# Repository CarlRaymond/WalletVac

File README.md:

# WalletVac
A unique donation accepting device

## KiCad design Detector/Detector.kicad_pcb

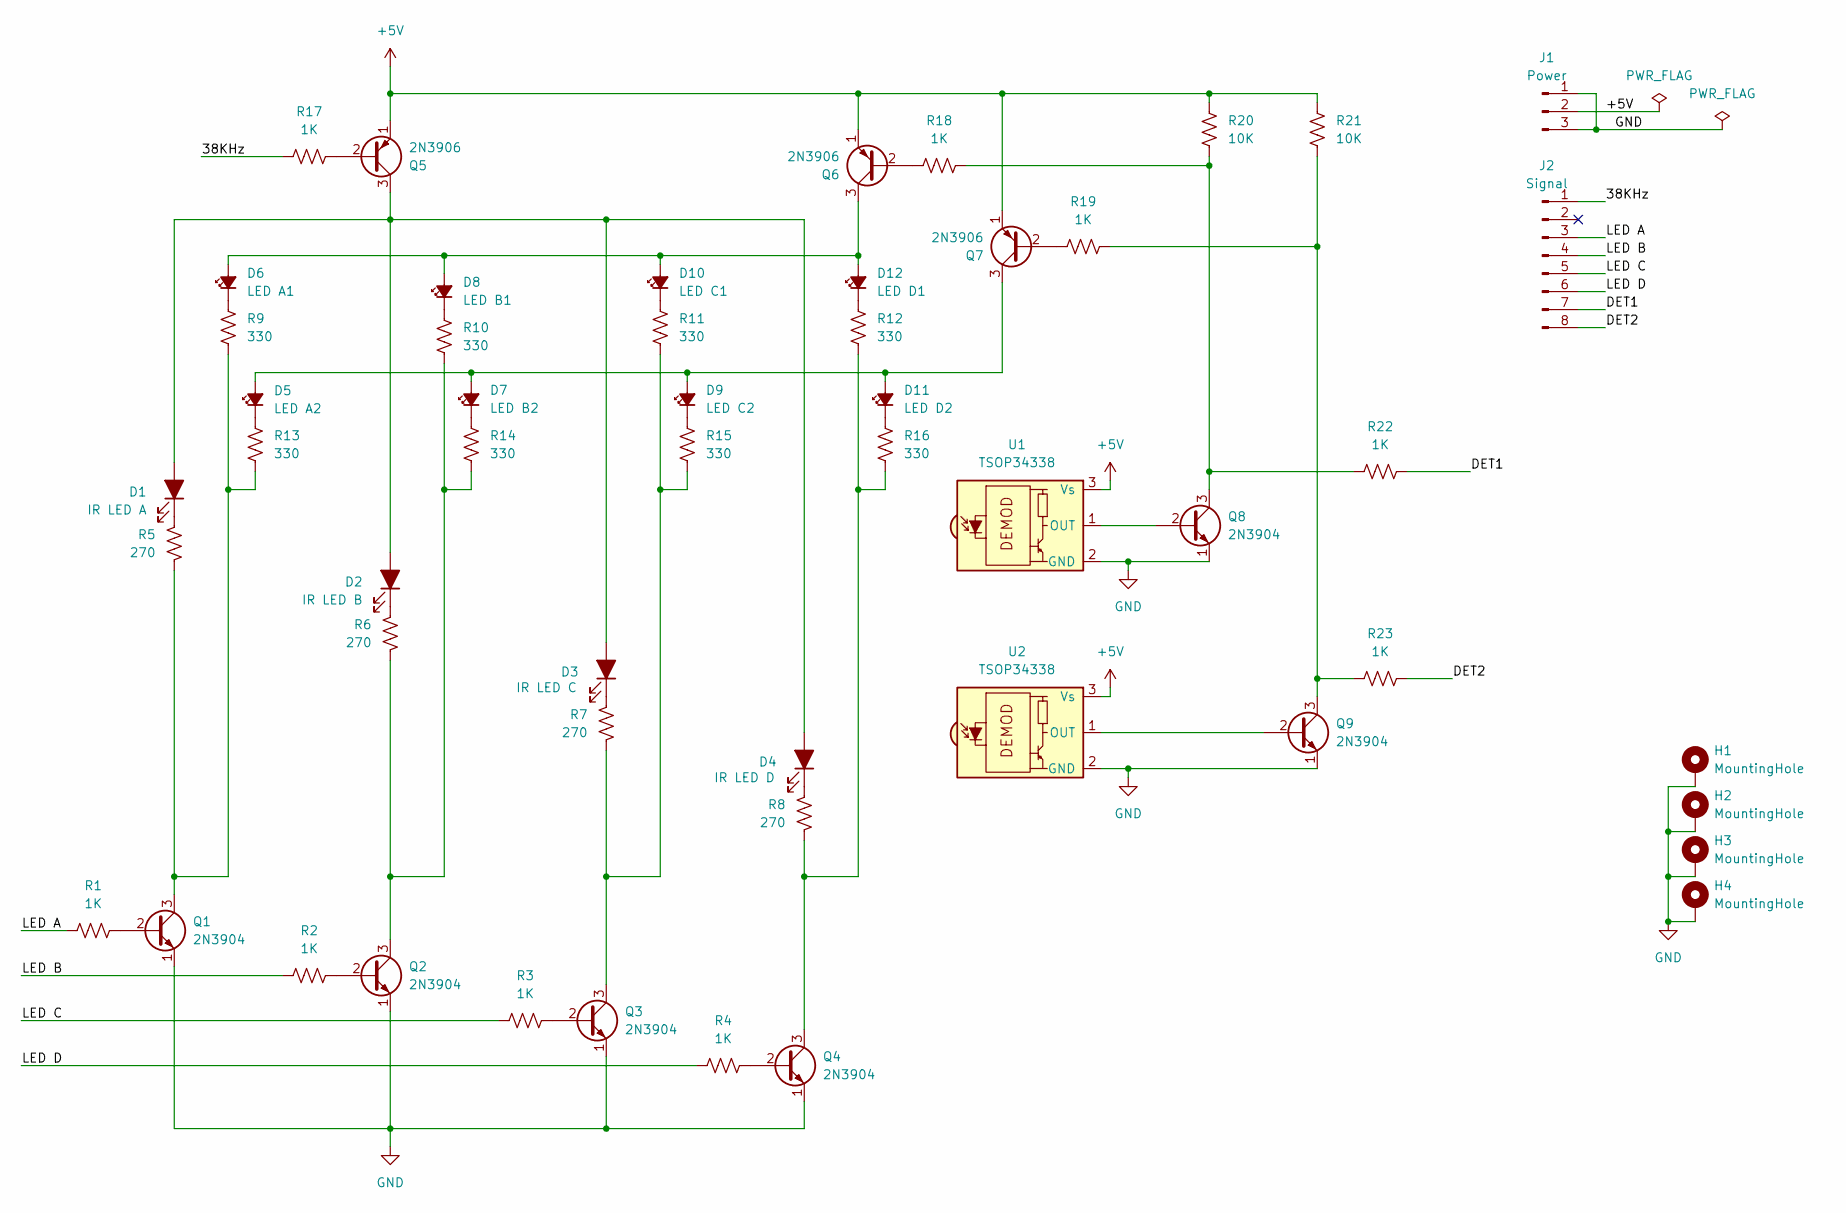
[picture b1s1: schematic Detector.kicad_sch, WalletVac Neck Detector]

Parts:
D1: IR LED A; LED_D5.0mm_Horizontal_O3.81mm_Z3.0mm
D2: IR LED B; LED_D5.0mm_Horizontal_O3.81mm_Z3.0mm
D3: IR LED C; LED_D5.0mm_Horizontal_O3.81mm_Z3.0mm
D4: IR LED D; LED_D5.0mm_Horizontal_O3.81mm_Z3.0mm
D5: LED A2; LED_D3.0mm
D6: LED A1; LED_D3.0mm
D7: LED B2; LED_D3.0mm
D8: LED B1; LED_D3.0mm
D9: LED C2; LED_D3.0mm
D10: LED C1; LED_D3.0mm
D11: LED D2; LED_D3.0mm
D12: LED D1; LED_D3.0mm
H1, H2, H3, H4: MountingHole; MountingHole_3.2mm_M3_DIN965_Pad_TopBottom
J1: Power; PinHeader_1x03_P2.54mm_Horizontal
J2: Signal; PinHeader_1x08_P2.54mm_Horizontal
Q1, Q2, Q3, Q4, Q8, Q9: 2N3904; TO-92_Inline
Q5, Q6, Q7: 2N3906; TO-92_Inline
R1, R2, R3, R4, R17, R18, R19, R22, R23: 1K; R_Axial_DIN0207_L6.3mm_D2.5mm_P7.62mm_Horizontal
R5, R6, R7, R8: 270; R_Axial_DIN0207_L6.3mm_D2.5mm_P7.62mm_Horizontal
R9, R10, R11, R12, R13, R14, R15, R16: 330; R_Axial_DIN0207_L6.3mm_D2.5mm_P7.62mm_Horizontal
R20, R21: 10K; R_Axial_DIN0207_L6.3mm_D2.5mm_P7.62mm_Horizontal
U1, U2: TSOP34338; Vishay_MOLD-3Pin

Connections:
+5V: J1.2, Q5.1 (E), Q6.1 (E), Q7.1 (E), R20.1, R21.1, U1.3 (Vs), U2.3 (Vs)
/38KHz: J2.1, R17.1
/DET1: J2.7, R22.2
/DET2: J2.8, R23.2
/LED A: J2.3, R1.1
/LED B: J2.4, R2.1
/LED C: J2.5, R3.1
/LED D: J2.6, R4.1
GND: H1.1, H2.1, H3.1, H4.1, J1.1, J1.3, Q1.1 (E), Q2.1 (E), Q3.1 (E), Q4.1 (E), Q8.1 (E), Q9.1 (E), U1.2 (GND), U2.2 (GND)
unnamed: D1.2 (A), D2.2 (A), D3.2 (A), D4.2 (A), Q5.3 (C)
unnamed: D1.1 (K), R5.1
unnamed: D2.1 (K), R6.1
unnamed: D3.1 (K), R7.1
unnamed: D4.1 (K), R8.1
unnamed: D5.1 (K), R13.1
unnamed: D6.1 (K), R9.1
unnamed: D7.1 (K), R14.1
unnamed: D8.1 (K), R10.1
unnamed: D9.1 (K), R15.1
unnamed: D6.2 (A), D8.2 (A), D10.2 (A), D12.2 (A), Q6.3 (C)
unnamed: D10.1 (K), R11.1
unnamed: D5.2 (A), D7.2 (A), D9.2 (A), D11.2 (A), Q7.3 (C)
unnamed: D11.1 (K), R16.1
unnamed: D12.1 (K), R12.1
unnamed: Q1.2 (B), R1.2
unnamed: Q1.3 (C), R5.2, R9.2, R13.2
unnamed: Q2.2 (B), R2.2
unnamed: Q2.3 (C), R6.2, R10.2, R14.2
unnamed: Q3.2 (B), R3.2
unnamed: Q3.3 (C), R7.2, R11.2, R15.2
unnamed: Q4.2 (B), R4.2
unnamed: Q4.3 (C), R8.2, R12.2, R16.2
unnamed: Q5.2 (B), R17.2
unnamed: Q6.2 (B), R18.1
unnamed: Q7.2 (B), R19.1
unnamed: Q8.2 (B), U1.1 (OUT)
unnamed: Q8.3 (C), R18.2, R20.2, R22.1
unnamed: Q9.2 (B), U2.1 (OUT)
unnamed: Q9.3 (C), R19.2, R21.2, R23.1

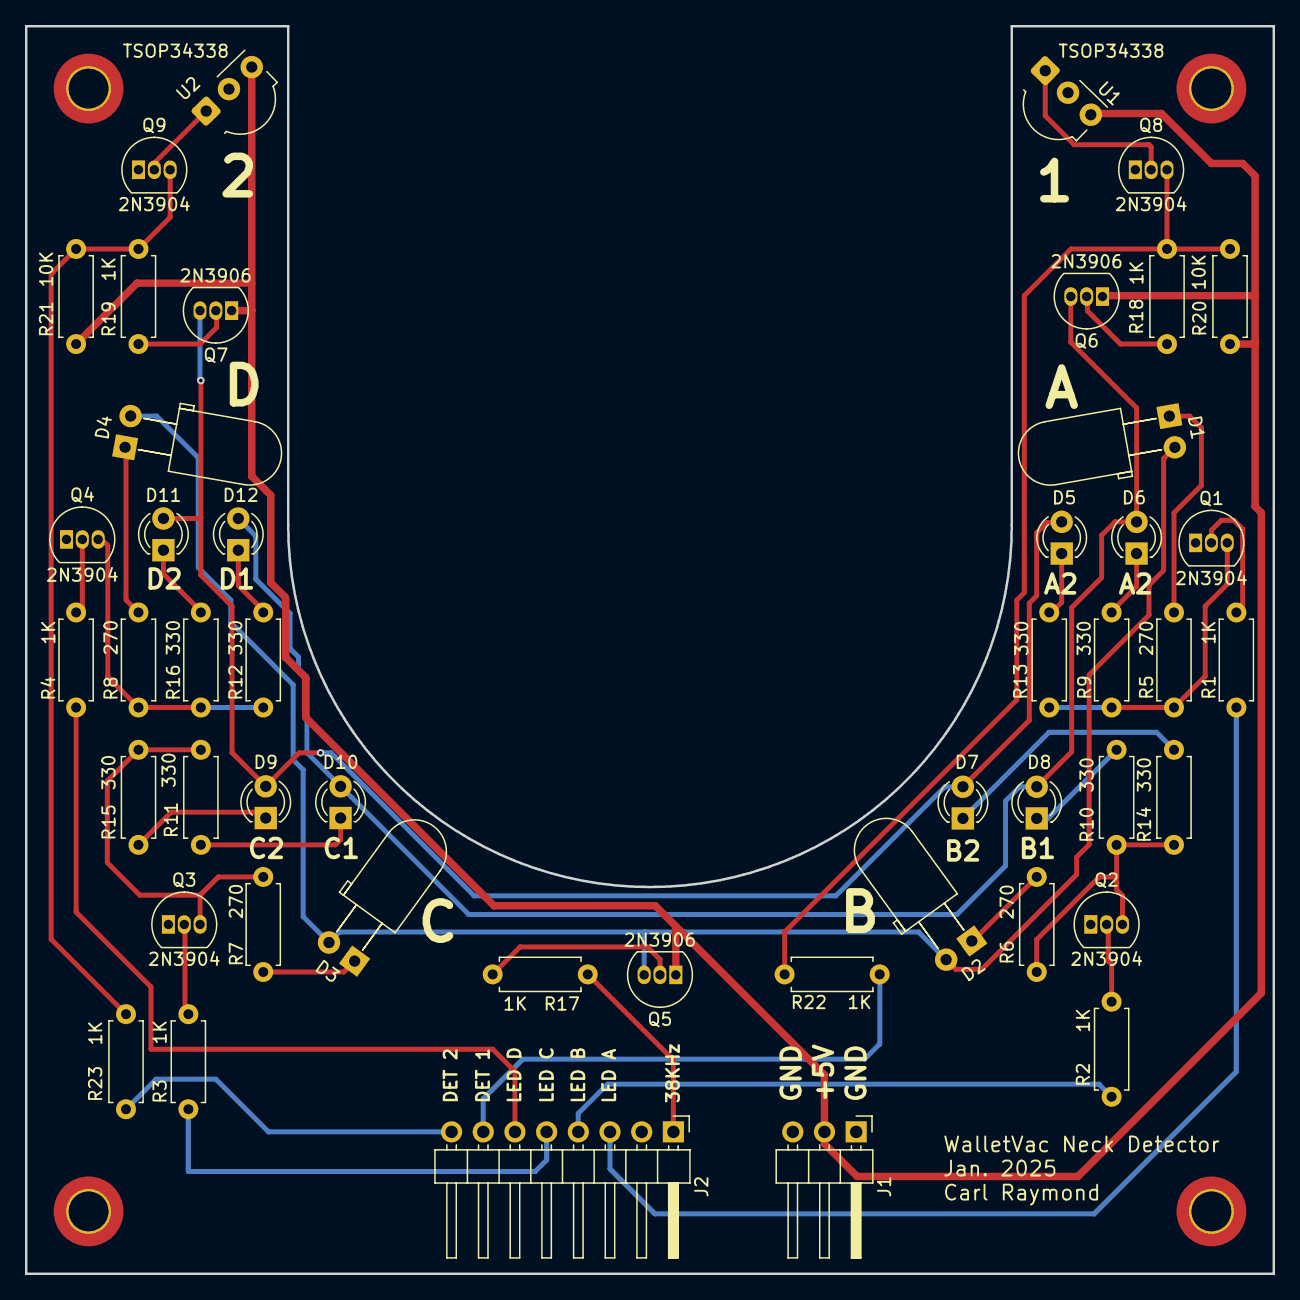
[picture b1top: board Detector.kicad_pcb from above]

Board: 2 copper layers, 100.0 x 100.0 mm, 52 parts (0 on the bottom side), 39 nets.

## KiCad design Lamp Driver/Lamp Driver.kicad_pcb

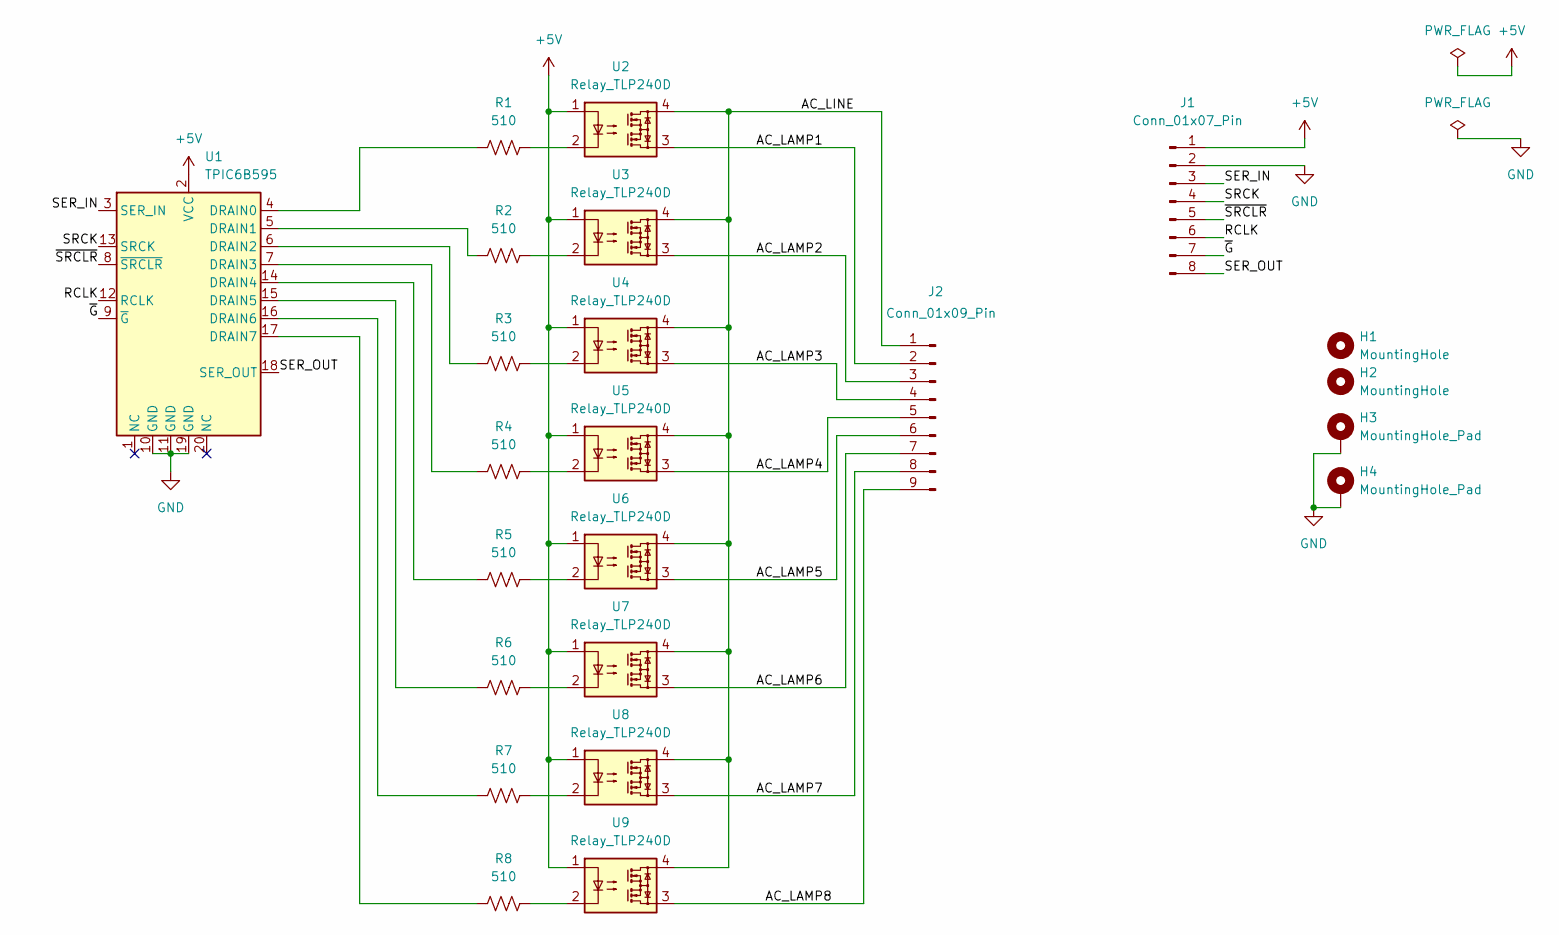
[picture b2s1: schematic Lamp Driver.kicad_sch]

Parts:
H1, H2: MountingHole; MountingHole_3.2mm_M3_ISO14580
H3, H4: MountingHole_Pad; MountingHole_3.2mm_M3_DIN965_Pad
J1: Conn_01x07_Pin; PinHeader_1x08_P2.54mm_Horizontal
J2: Conn_01x09_Pin; TerminalBlock_Phoenix_MKDS-1,5-9-5.08_1x09_P5.08mm_Horizont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
R1, R2, R3, R4, R5, R6, R7, R8: 510; R_0805_2012Metric_Pad1.20x1.40mm_HandSolder
U1: TPIC6B595; SOIC-20W_7.5x12.8mm_P1.27mm
U2, U3, U4, U5, U6, U7, U8, U9: Relay_TLP240D; TLP240D LF1

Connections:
+5V: J1.1, U1.2 (VCC), U2.1, U3.1, U4.1, U5.1, U6.1, U7.1, U8.1, U9.1
/AC_LAMP1: J2.2, U2.3
/AC_LAMP2: J2.3, U3.3
/AC_LAMP3: J2.4, U4.3
/AC_LAMP4: J2.5, U5.3
/AC_LAMP5: J2.6, U6.3
/AC_LAMP6: J2.7, U7.3
/AC_LAMP7: J2.8, U8.3
/AC_LAMP8: J2.9, U9.3
/AC_LINE: J2.1, U2.4, U3.4, U4.4, U5.4, U6.4, U7.4, U8.4, U9.4
/RCLK: J1.6, U1.12 (RCLK)
/SER_IN: J1.3, U1.3 (SER_IN)
/SER_OUT: J1.8, U1.18 (SER_OUT)
/SRCK: J1.4, U1.13 (SRCK)
/~G: J1.7, U1.9 (~G)
/~SRCLR: J1.5, U1.8 (~SRCLR)
GND: H3.1, H4.1, J1.2, U1.10 (GND), U1.11 (GND), U1.19 (GND)
unnamed: R1.2, U2.2
unnamed: R2.2, U3.2
unnamed: R3.2, U4.2
unnamed: R4.2, U5.2
unnamed: R5.2, U6.2
unnamed: R6.2, U7.2
unnamed: R7.2, U8.2
unnamed: R8.2, U9.2
unnamed: R1.1, U1.4 (DRAIN0)
unnamed: R2.1, U1.5 (DRAIN1)
unnamed: R3.1, U1.6 (DRAIN2)
unnamed: R4.1, U1.7 (DRAIN3)
unnamed: R5.1, U1.14 (DRAIN4)
unnamed: R6.1, U1.15 (DRAIN5)
unnamed: R7.1, U1.16 (DRAIN6)
unnamed: R8.1, U1.17 (DRAIN7)

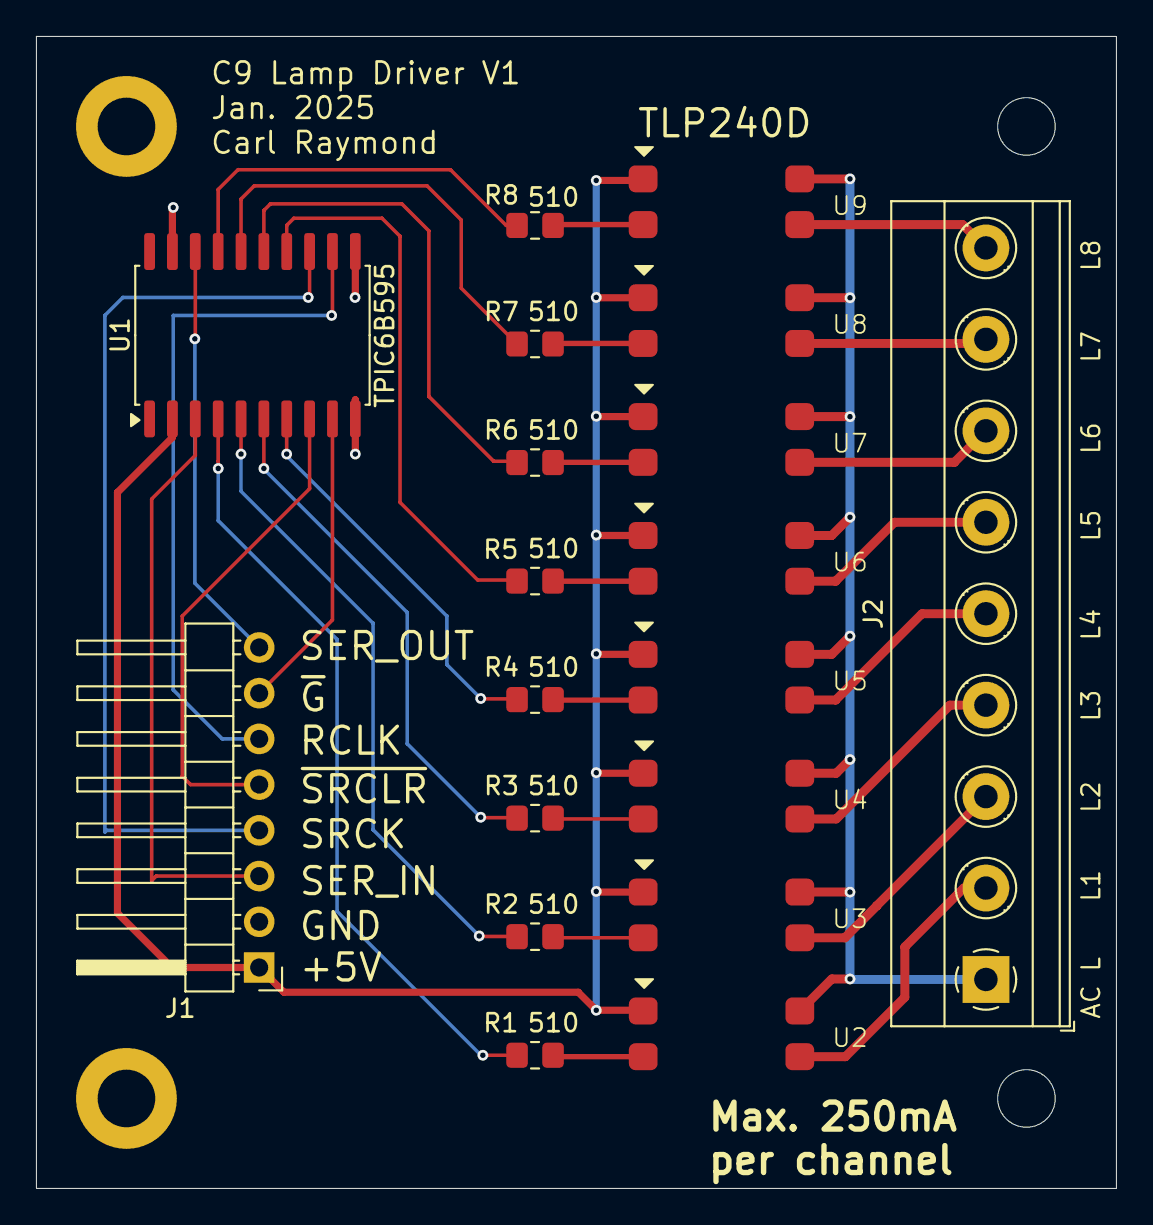
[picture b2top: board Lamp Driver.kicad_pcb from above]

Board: 2 copper layers, 60.0 x 64.0 mm, 23 parts (0 on the bottom side), 33 nets.

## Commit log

2024-12-16 Produces 38Khz on pin 9, bell ringer on pin 13
2024-12-18 Produce inverted output on pin 12
2024-12-31 Add solenoid driver diagram
2025-01-06 Add neck detector
2025-01-07 More placement and routing
2025-01-20 Rename code folder
    WalletVac/Controller/WalletVac => WalletVac/Controller/Code
2025-01-20 Update detector borad
2025-01-20 Add lamp driver
2025-01-25 Configure 10ms interrupt
2025-01-25 Add \.pio to .gitignore
2025-01-25 PlatformIO created
2025-01-26 Add 4th LED
2025-02-03 Change pin map, increase scan rate
